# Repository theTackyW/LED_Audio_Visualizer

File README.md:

# LED_Audio_Visualizer
### Light DJ project

- This personal project utilizes MSGEQ7 to divide incoming audio signal into seven frequency bands and represents them as spectrum on 7 corresponding NeoPixel Sticks
Audio signal can be recieved by either a 3.5mm headphone jack or a microphone.

## Arduino Program and Functions
### LED_Audio_Visualizer.ino

> **void loop()**
> 
> - main function that read outputs of MSGEQ7, volume sensitivity nobe(volSen), and brightness nobe(brightControl); Update NeoPixel Sticks status.

> **void SingleLED(int v, int band)**
> 
> - Reads the output from MSGEQ7 for one specific band. Compare value with threadholds to determine how many LEDs need to be light up for each band

> **void setLEDnum(int n, int band, double bright)**
> 
> - function that uses .setPixelColor() function in the included <Adafruit_NeoPixel.h>. Considers brightness and color.
> calls the colorFade functions for color fade from [r1,g1,b1] to [r2,g2,b2] based on band level

> **void clearAll(int band)**
> 
> - set all LEDs on one band to OFF

> **double colorFadeR(int r1, int r2, int n)**

> **double colorFadeG(int g1, int g2, int n)**

> **double colorFadeB(int b1, int b2, int n)**

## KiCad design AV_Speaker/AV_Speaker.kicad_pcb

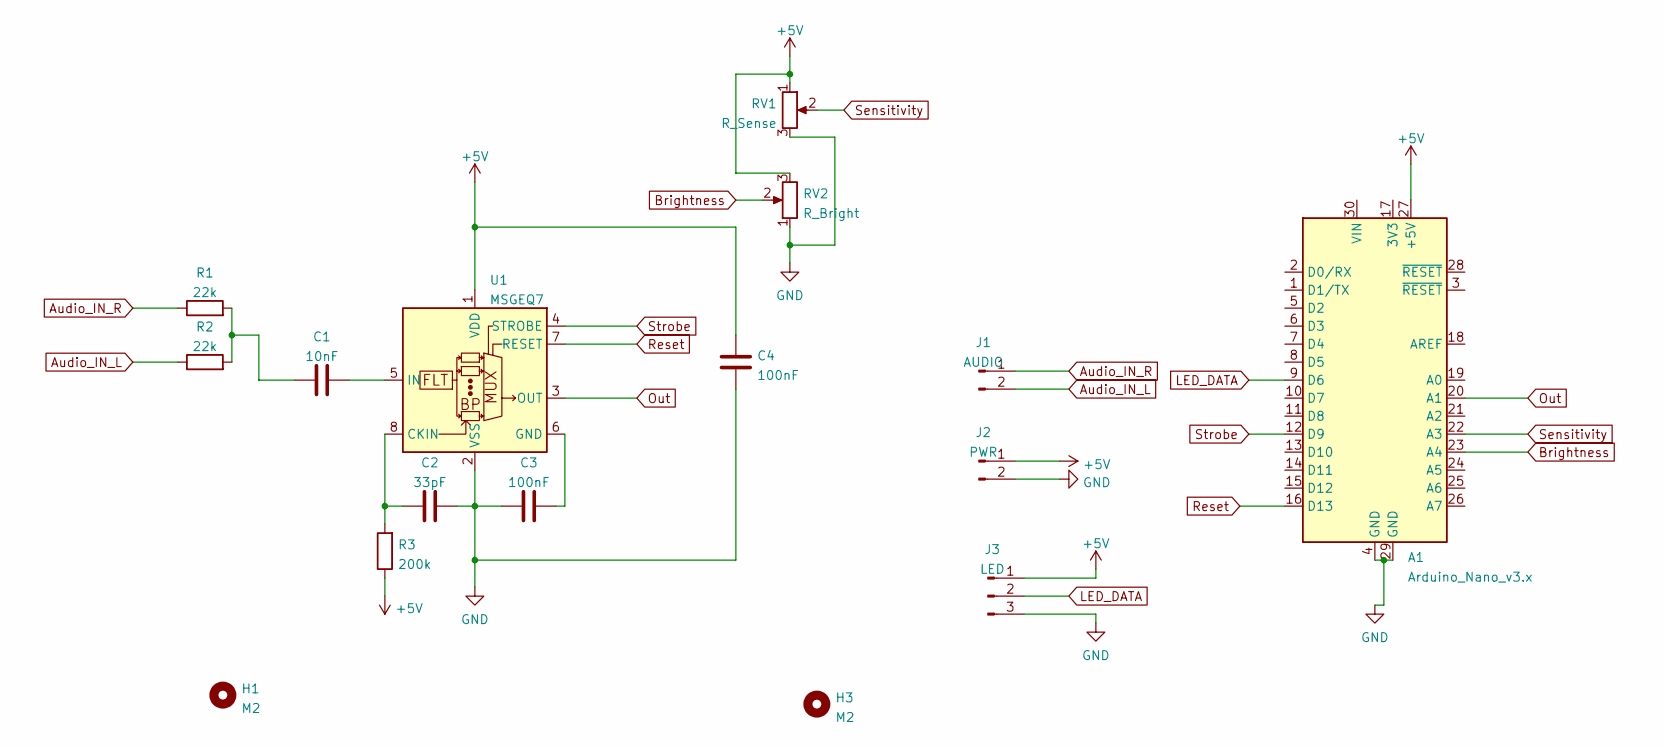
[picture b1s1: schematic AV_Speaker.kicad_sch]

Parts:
A1: Arduino_Nano_v3.x; Arduino_Nano
C1: 10nF; C_Disc_D4.3mm_W1.9mm_P5.00mm
C2: 33pF; C_Disc_D4.3mm_W1.9mm_P5.00mm
C3, C4: 100nF; C_Disc_D4.3mm_W1.9mm_P5.00mm
H1, H3: M2; MountingHole_2.2mm_M2
J1: AUDIO; PinHeader_1x02_P2.54mm_Vertical
J2: PWR; PinHeader_1x02_P2.54mm_Vertical
J3: LED; PinHeader_1x03_P2.54mm_Vertical
R1, R2: 22k; R_Axial_DIN0207_L6.3mm_D2.5mm_P7.62mm_Horizontal
R3: 200k; R_Axial_DIN0207_L6.3mm_D2.5mm_P7.62mm_Horizontal
RV1: R_Sense; Potentiometer_Piher_PC-16_Single_Horizontal
RV2: R_Bright; Potentiometer_Piher_PC-16_Single_Horizontal
U1: MSGEQ7; DIP-8_W7.62mm_LongPads

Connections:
+5V: A1.27 (+5V), C4.2, J2.1, J3.1, R3.1, RV1.1, RV2.3, U1.1 (VDD)
Audio_IN_L: J1.2, R2.1
Audio_IN_R: J1.1, R1.1
Brightness: A1.23 (A4), RV2.2
GND: A1.4 (GND), A1.29 (GND), C2.2, C3.1, C4.1, J2.2, J3.3, RV1.3, RV2.1, U1.2 (VSS)
LED_DATA: A1.9 (D6), J3.2
unnamed: C1.1, R1.2, R2.2
unnamed: C1.2, U1.5 (IN)
unnamed: C2.1, R3.2, U1.8 (CKIN)
unnamed: C3.2, U1.6 (GND)
Out: A1.20 (A1), U1.3 (OUT)
Reset: A1.16 (D13), U1.7 (RESET)
Sensitivity: A1.22 (A3), RV1.2
Strobe: A1.12 (D9), U1.4 (STROBE)

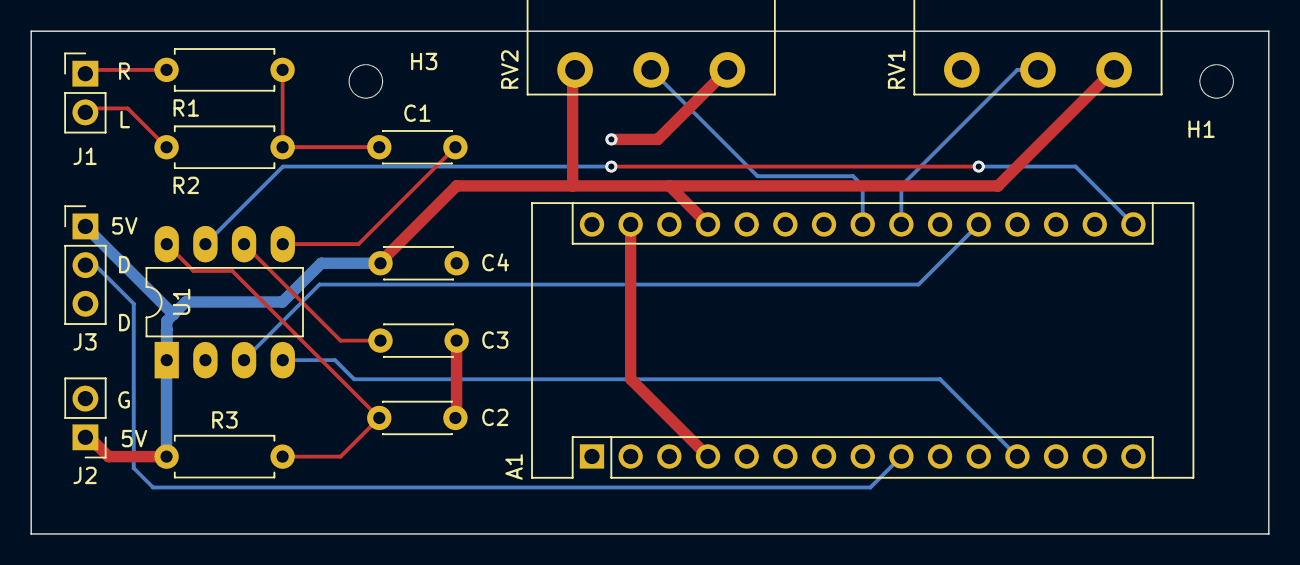
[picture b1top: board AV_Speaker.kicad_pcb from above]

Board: 2 copper layers, 81.3 x 33.0 mm, 16 parts (0 on the bottom side), 14 nets.

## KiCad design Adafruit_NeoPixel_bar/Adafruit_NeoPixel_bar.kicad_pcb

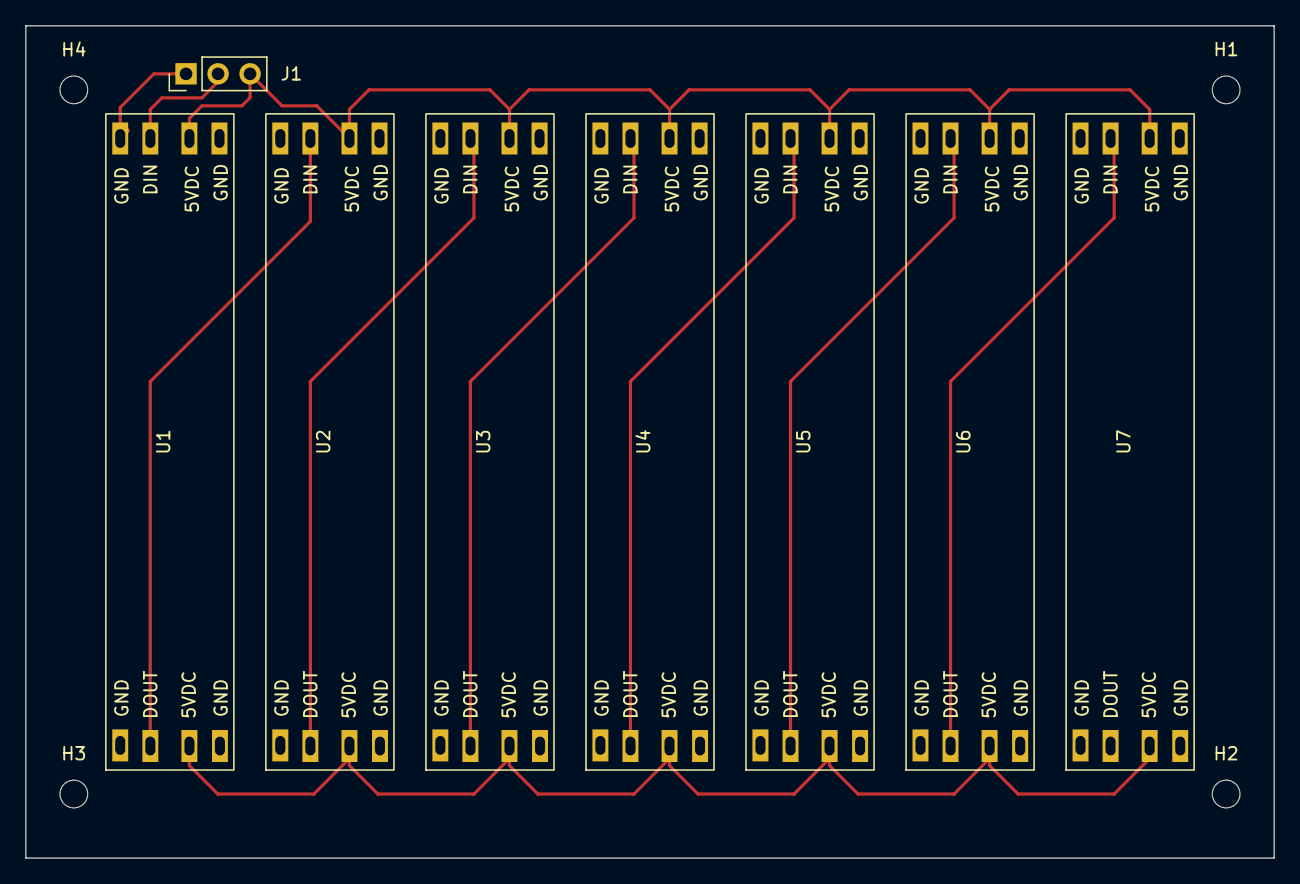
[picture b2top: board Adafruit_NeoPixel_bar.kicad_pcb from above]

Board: 2 copper layers, 99.1 x 66.0 mm, 12 parts (0 on the bottom side), 9 nets.

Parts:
H1, H2, H3, H4: M2; MountingHole_2.2mm_M2
J1: 1x3; PinHeader_1x03_P2.54mm_Vertical
U1, U2, U3, U4, U5, U6, U7: NeoPixel_bar

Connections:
+5V: J1.3, U1.5VDC, U2.5VDC, U3.5VDC, U4.5VDC, U5.5VDC, U6.5VDC, U7.5VDC
GND: J1.1, U1.GND, U2.GND, U3.GND, U4.GND, U5.GND, U6.GND, U7.GND
unnamed: J1.2, U1.DIN
unnamed: U1.DOUT, U2.DIN
unnamed: U2.DOUT, U3.DIN
unnamed: U3.DOUT, U4.DIN
unnamed: U4.DOUT, U5.DIN
unnamed: U5.DOUT, U6.DIN
unnamed: U6.DOUT, U7.DIN

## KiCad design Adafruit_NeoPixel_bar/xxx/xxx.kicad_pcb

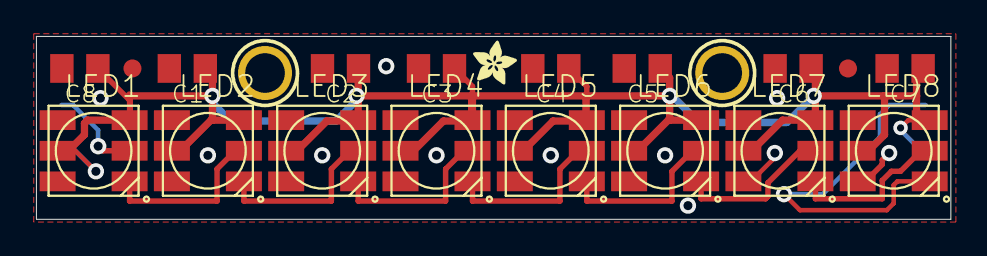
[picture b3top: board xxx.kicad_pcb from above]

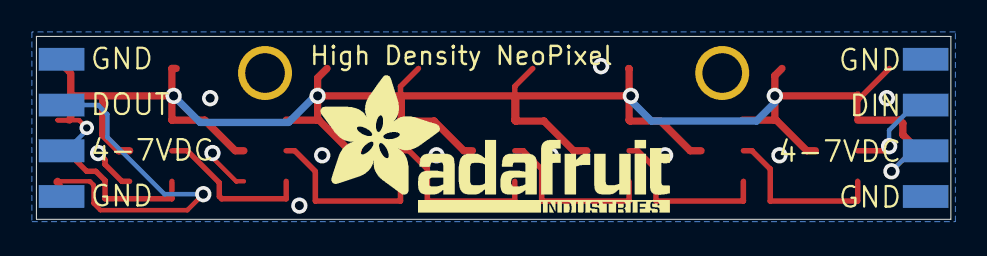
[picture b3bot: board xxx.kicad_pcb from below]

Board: 2 copper layers, 50.8 x 10.2 mm, 24 parts (3 on the bottom side), 11 nets.

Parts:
C1, C2, C3, C4, C5, C6, C7, C8: C0805K
CN1, CN2: 1X4SMT; 1X4-SMT
FID1, FID3: FIDUCIAL""; FIDUCIAL_1MM
LED1, LED2, LED3, LED4, LED5, LED6, LED7, LED8: WS28115050
U$1: ADAFRUIT_TEXT_20MM
U$2, U$3: MOUNTINGHOLE2.0; MOUNTINGHOLE_2.0_PLATED
U$4: ADAFRUIT_2.5MM

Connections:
+5V: C1.1, C2.1, C3.1, C4.1, C5.1, C6.1, C7.1, C8.1, CN1.3, CN2.2, LED1.LEDVDD, LED1.VDD, LED2.LEDVDD, LED2.VDD, LED3.LEDVDD, LED3.VDD, LED4.LEDVDD, LED4.VDD, LED5.LEDVDD, LED5.VDD, LED6.LEDVDD, LED6.VDD, LED7.LEDVDD, LED7.VDD, LED8.LEDVDD, LED8.VDD
GND: C1.2, C2.2, C3.2, C4.2, C5.2, C6.2, C7.2, C8.2, CN1.1, CN1.4, CN2.1, CN2.4, LED1.VSS, LED2.VSS, LED3.VSS, LED4.VSS, LED5.VSS, LED6.VSS, LED7.VSS, LED8.VSS
unnamed: LED1.DO, LED2.DI
unnamed: LED2.DO, LED3.DI
unnamed: LED3.DO, LED4.DI
unnamed: LED4.DO, LED5.DI
unnamed: LED5.DO, LED6.DI
unnamed: LED6.DO, LED7.DI
unnamed: LED7.DO, LED8.DI
unnamed: CN2.3, LED1.DI
unnamed: CN1.2, LED8.DO

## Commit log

2022-01-11 Fix formatting
    Deleted some unused code and comments
2022-01-11 Fix formatting issues
2022-01-13 Added color-fading functionality
    colorFadeR/G/B() functions fades between two colors--based on amplitude of the frequency band
2022-04-19 Update LED_Audio_Visualizer.ino
    Changed fading colors
2022-07-26 Big Update
    Updated CAD case design; code for Nano; code for actual orientation of the LED matrix
